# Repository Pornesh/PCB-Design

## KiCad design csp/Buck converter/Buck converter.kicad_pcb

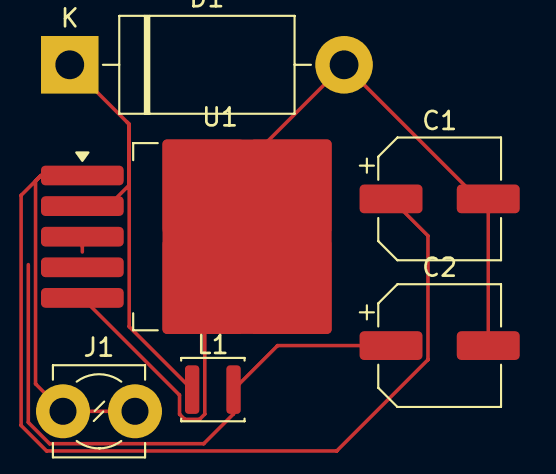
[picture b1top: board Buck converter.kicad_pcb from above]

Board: 2 copper layers, 6 parts (0 on the bottom side), 4 nets.

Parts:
C1, C2: C; CP_Elec_6.3x3
D1: 1N5820; D_DO-201AD_P15.24mm_Horizontal
J1: Conn_01x02; TerminalBlock_MetzConnect_360410_1x01_Horizontal_ScrewM3.0
L1: L; L_APV_ANR3010
U1: LM2596S-5; TO-263-5_TabPin3

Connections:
+3.3V: C1.1, J1.1, U1.1 (VIN)
GND: C1.2, C2.2, D1.2 (A), U1.3 (GND), U1.5 (~ON/OFF)
unnamed: D1.1 (K), L1.1, U1.2 (OUT)
VCC: C2.1, L1.2, U1.4 (FB)

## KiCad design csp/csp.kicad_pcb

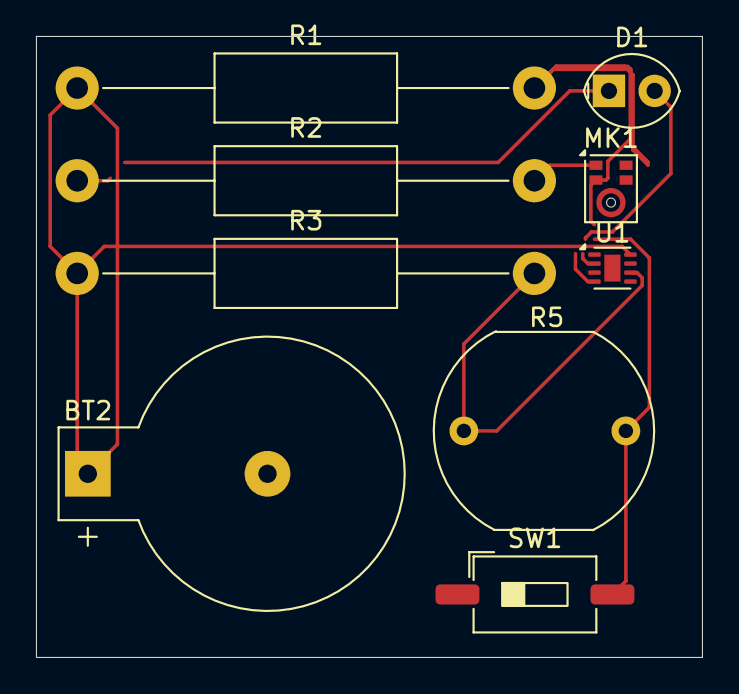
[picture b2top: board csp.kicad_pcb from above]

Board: 2 copper layers, 37.0 x 34.5 mm, 9 parts (0 on the bottom side), 6 nets.

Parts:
BT2: Battery_Cell; BatteryHolder_Keystone_500
D1: LED; LED_Oval_W5.2mm_H3.8mm
MK1: Microphone_Condenser; Knowles_LGA-5_3.5x2.65mm
R1, R2, R3: R; R_Axial_DIN0411_L9.9mm_D3.6mm_P25.40mm_Horizontal
R5: LDR07; R_LDR_12x10.8mm_P9.0mm_Vertical
SW1: SW_SPST_Lamp; SW_DIP_SPSTx01_Slide_6.7x4.1mm_W8.61mm_P2.54mm_LowProfile
U1: ATtiny85-20P; DFN-8-1EP_2x2mm_P0.5mm_EP0.9x1.5mm

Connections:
+3.3V: BT2.1 (+), R1.1, R3.1, U1.8 (VCC)
/ldr: R3.2, R5.1, U1.6 (PB1)
/led: D1.2 (A), U1.2 (XTAL1/PB3)
/mic: MK1.2 (+), R1.2, U1.7 (PB2)
GND: MK1.1 (-), R2.2, R5.2, SW1.2, U1.4 (GND)
unnamed: D1.1 (K), R2.1

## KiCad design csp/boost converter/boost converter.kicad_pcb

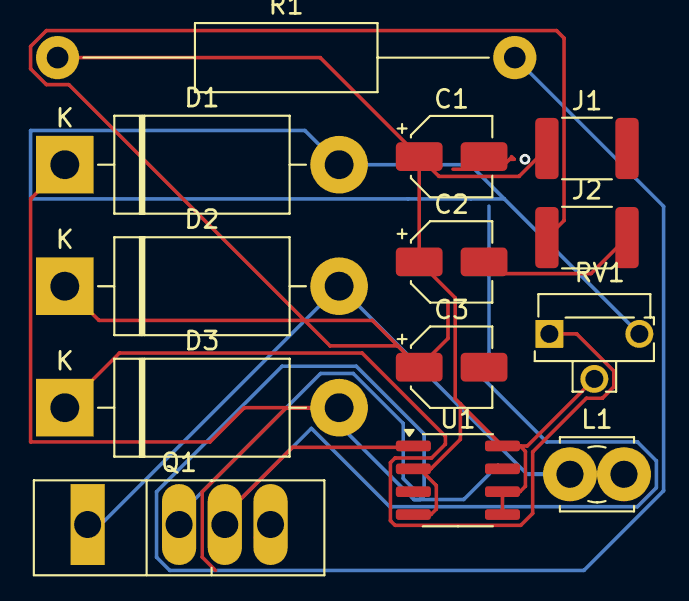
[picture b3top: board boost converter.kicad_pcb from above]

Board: 2 copper layers, 13 parts (0 on the bottom side), 8 nets.

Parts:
C1, C2, C3: C; CP_Elec_4x3
D1, D3: D; D_DO-201AD_P15.24mm_Horizontal
D2: 1N5822; D_DO-201AD_P15.24mm_Horizontal
J1, J2: Screw_Terminal_01x02; L_1812_4532Metric_Pad1.30x3.40mm_HandSolder
L1: L; TerminalBlock_MetzConnect_360272_1x01_Horizontal_ScrewM2.6
Q1: BUK7880-55A; TO-247-4_Vertical
R1: R; R_Axial_DIN0411_L9.9mm_D3.6mm_P25.40mm_Horizontal
RV1: rv1; Potentiometer_Runtron_RM-063_Horizontal
U1: LM555xM; SOIC-8_3.9x4.9mm_P1.27mm

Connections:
GND: C1.2, C2.2, C3.2, J1.2, J2.2, Q1.3 (S), U1.1 (GND)
unnamed: D1.2 (A), RV1.3
unnamed: D1.1 (K), D3.2 (A), R1.2, U1.7 (DIS)
unnamed: D2.2 (A), L1.1, Q1.1 (G)
unnamed: C3.1, D2.1 (K), J2.1
unnamed: D3.1 (K), RV1.1
unnamed: C1.1, C2.1, J1.1, R1.1, RV1.2, U1.2 (TR), U1.4 (R), U1.5 (CV), U1.6 (THR), U1.8 (VCC)
unnamed: Q1.2 (D), U1.3 (Q)

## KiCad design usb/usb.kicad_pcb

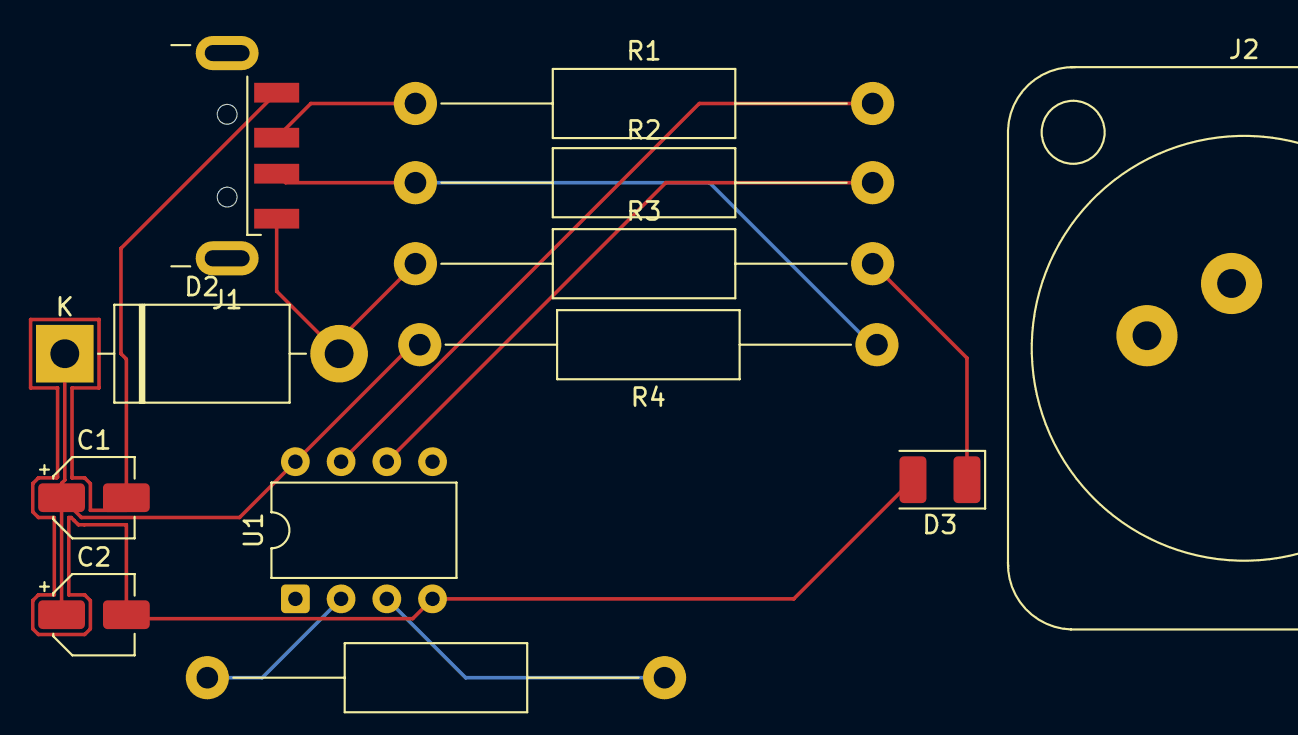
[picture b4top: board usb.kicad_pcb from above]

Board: 2 copper layers, 12 parts (0 on the bottom side), 10 nets.

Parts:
C1, C2: C; CP_Elec_4x3
D2: D; D_DO-201AD_P15.24mm_Horizontal
D3: LED; LED_PLCC-2_3.4x3.0mm_AK
J1: USB_A; USB_A_CNCTech_1001-011-01101_Horizontal
J2: 6P2C; Jack_speakON_Neutrik_NL2MDXX-V_Vertical
R1, R2, R3, R4, R5: R; R_Axial_DIN0411_L9.9mm_D3.6mm_P25.40mm_Horizontal
U1: ATtiny45-20P; DIP-8_W7.62mm

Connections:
GND: C1.2, C2.2, D3.1 (K), J1.4 (GND), U1.4 (GND)
unnamed: D2.2 (A), J1.1 (VBUS), R3.1
unnamed: C1.1, C2.1, D2.1 (K), R4.2, U1.8 (VCC)
unnamed: D3.2 (A), R3.2
unnamed: J1.3 (D+), R1.1
unnamed: J1.2 (D-), R2.1, R4.1
unnamed: R2.2, U1.6 (PB1)
unnamed: R1.2, U1.7 (PB2)
unnamed: R5.2, U1.2 (XTAL1/PB3)
unnamed: R5.1, U1.3 (XTAL2/PB4)
